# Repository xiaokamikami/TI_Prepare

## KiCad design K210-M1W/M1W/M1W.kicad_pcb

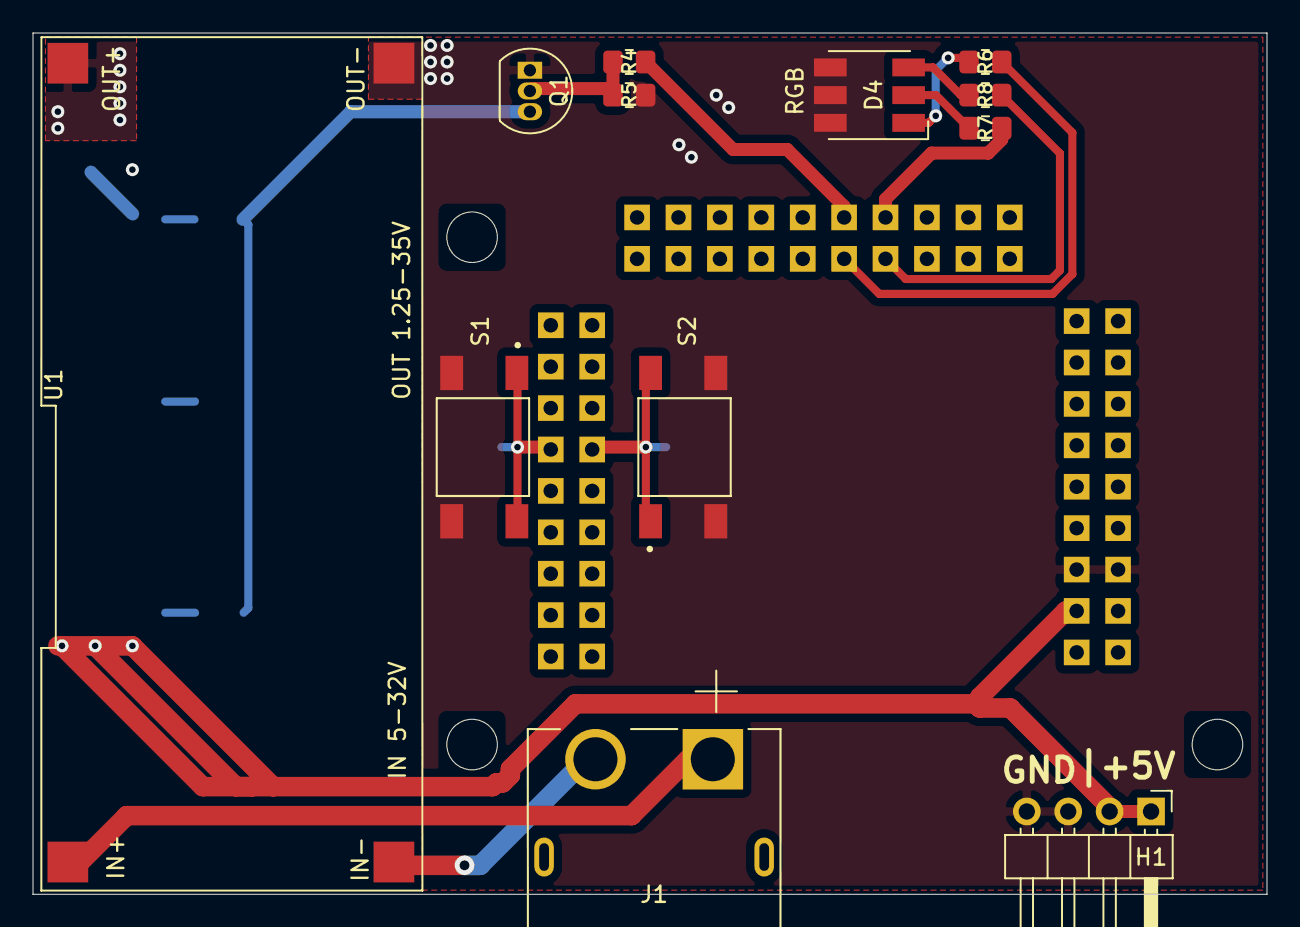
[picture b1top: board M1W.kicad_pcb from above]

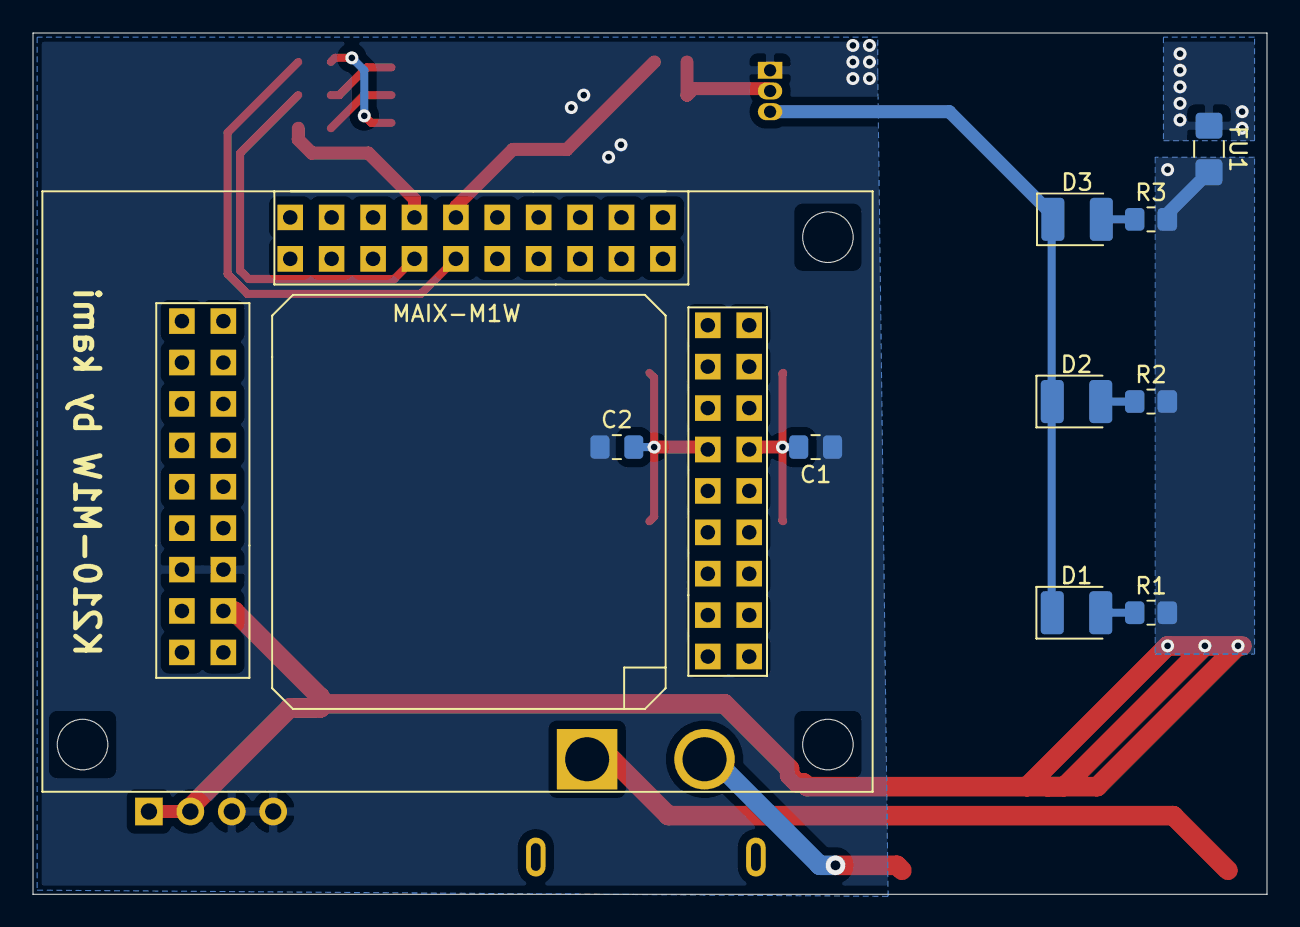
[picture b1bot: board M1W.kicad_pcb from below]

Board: 2 copper layers, 75.7 x 52.8 mm, 22 parts (10 on the bottom side), 19 nets.

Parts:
C1, C2: 100nf; C_0805_2012Metric_Pad1.18x1.45mm_HandSolder
D1, D2, D3: LED; LED_1210_3225Metric_Pad1.42x2.65mm_HandSolder
D4: LED_RGB; LED_RGB_5050-6
FU1: Fuse_Small; Fuse_1206_3216Metric_Castellated
H1: Hader-1*4; PinHeader_1x04_P2.54mm_Horizontal
J1: XT60PW-M; AMASS_XT60PW-M
MAIN1: maix_dock; MAIX_DOCK
Q1: S8050; TO-92_Inline
R1, R2, R3, R4, R5: 240R; R_0805_2012Metric_Pad1.20x1.40mm_HandSolder
R6, R7, R8: 470R; R_0805_2012Metric_Pad1.20x1.40mm_HandSolder
S1, S2: SW_1571527-1; SW-Push-Tur
U1: LM2596S; LM2596S-DC-DC-25-5V

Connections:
+5V: FU1.2, H1.1, H1.2, MAIN1.52, R1.2, R2.2, R3.2
GND: C1.1, C2.1, D4.4, D4.5, D4.6, H1.3, H1.4, MAIN1.54, MAIN1.55, Q1.1, R5.2, S1.3, S1.4, S2.3, S2.4, U1.3
IO8_LED: MAIN1.26, R4.2
Key1: C1.2, MAIN1.10, S1.1, S1.2
Key2: C2.2, MAIN1.11, S2.1, S2.2
unnamed: D1.1, D2.1, D3.1, Q1.3
unnamed: D1.2, R1.1
unnamed: D2.2, R2.1
unnamed: D3.2, R3.1
unnamed: D4.1, R6.1
unnamed: D4.2, R7.1
unnamed: D4.3, R8.1
unnamed: FU1.1, U1.4
unnamed: J1.1, U1.1
unnamed: J1.2, U1.2
unnamed: Q1.2, R4.1, R5.1
RGB5050-B: MAIN1.29, R8.2
RGB5050-G: MAIN1.28, R7.2
RGB5050-R: MAIN1.27, R6.2

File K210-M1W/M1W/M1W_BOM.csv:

"Comment","Description","Designator","Footprint","LibRef","Pins","Quantity","PartNumber","url",
"LED_RGB","desc","D4,","LED_RGB_5050-6","libref","6","1","","",
"240R","desc","R4,R5,","R_0805_2012Metric_Pad1.20x1.40mm_HandSolder","libref","2","2","","",
"470R","desc","R6,R7,R8,","R_0805_2012Metric_Pad1.20x1.40mm_HandSolder","libref","2","3","","",
"SW_1571527-1","desc","S1,S2,","SW-Push-Tur","libref","4","2","","",
"LM2596S","desc","U1,","LM2596S-DC-DC-25-5V","libref","4","1","","",
"100nf","desc","C1,C2,","C_0805_2012Metric_Pad1.18x1.45mm_HandSolder","libref","2","2","","",
"LED","desc","D1,D2,D3,","LED_1210_3225Metric_Pad1.42x2.65mm_HandSolder","libref","2","3","","",
"240R","desc","R1,R2,R3,","R_0805_2012Metric_Pad1.20x1.40mm_HandSolder","libref","2","3","","",
"Fuse_Small","desc","FU1,","Fuse_1206_3216Metric_Castellated","libref","2","1","","",
"Through Hole Items ",
"Hader-1*4","desc","H1,","PinHeader_1x04_P2.54mm_Horizontal","libref","4","1","","",
"XT60PW-M","desc","J1,","AMASS_XT60PW-M","libref","4","1","","",
"S8050","desc","Q1,","TO-92_Inline","libref","3","1","","",
"maix_dock","desc","MAIN1,","MAIX_DOCK","libref","59","1","","",

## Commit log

2021-07-31 180度舵机标签跟随完成
2021-08-01 ATK_IMU串口读写数据完成
2021-08-01 平衡车代码(待调试)
2021-08-02 平衡车代码 立直环调好
2021-10-11 小球颜色识别
2021-10-11 添加小球测试代码
2021-10-14 优化了识别率
2021-10-19 k210拓展板
2021-10-20 小车二代
2021-10-21 机械爪，舵机转向测试完成
2021-10-22 调试基础模块完成
2021-10-23 编码器功能完成
2021-10-24 修复了拓展板BUG
2021-10-24 新增串口不定长接收功能
2021-10-25 增加JSON解析，对接K210
2021-10-26 更新识别显示与串口通信功能
2021-10-27 PID调试完成
2021-10-27 添加补光灯
2021-10-28 更新抓球逻辑
2021-10-29 数据集快速增量
2021-10-29 备份模型1
2021-10-30 模型更新
2021-11-01 升级模型
2021-11-02 增加动态帧率限制
